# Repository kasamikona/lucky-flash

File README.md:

# Lucky Guitar Flashcart
A custom flashcart for the Lucky Group electronic guitar toy (らっき組 ギター) RK-001, made by People Co., Ltd.  

## What's it for?
The guitar toy, which I will call the Lucky Guitar from here onwards, has multiple play modes.
One of these modes uses ROM cartridges containing songs which you can play along with.
The songs are stored as MIDI files containing chord information.  

There were 14 main cartridges made, focusing on certain genres or artists,
and an additional "demo" cartridge containing a compilation of songs from the others.
The Lucky Guitar came with 2 or 3 random cartridges in the box, though additional ones could be purchased.
As it was a relatively obscure device, the cartridges are quite rare and it is very hard to collect them all.  

To allow the Lucky Guitar to be enjoyed to its fullest, I have developed a flash cart based heavily on the original cartridge design.
It supports playing ROM dumps of existing cartridges, as well as custom ROMs made from your own suitable MIDI files.
The latest version supports up to 8 different ROMs on one cartridge, with DIP switches to select them.  

Due to their small size, the flash carts contain no active logic and must be programmed externally.
Currently this is done through a custom adapter stackup for the TL866 (aka "MiniPro") Universal Programmer.
The stackup consists of a SN001-1 aka TSOP48 V3 base board from XinGong Tech, and the custom cartridge interface from here.
This adapter stack also allows dumping ROMs from the original cartridges after some modifications.  

## Contents
The main files you will want for making and using the flash cart are:
- **CartFlashMulti**: the latest multi-bank flash cart with DIP switches, intended for use with the custom shell. Gerber files coming soon.
- **LuckyCartInterface-TL866**: flash programmer interface for the TL866 and SN001-1. Gerber files coming soon.
- **CartShell.scad**: custom cart shell for the multi-bank flash cart, designed for SLA 3D printing. Render the main and cover parts separately. STL files coming soon.
- **CartParts.kicad_sym / CartParts.pretty**: custom KiCad parts shared between all PCBs.

The repo contains these additional files:
- **CartReplica**: a copy of the original cart PCB for research and analysis.
- **CartFlashSingle**: a flash cart based on the original carts, with minimal changes to support externally programming a flash chip. This can fit in an original shell.
- **DIP48-SN001**: a helper board that theoretically allows the cart interface to be used on other programming devices with 48-pin sockets.

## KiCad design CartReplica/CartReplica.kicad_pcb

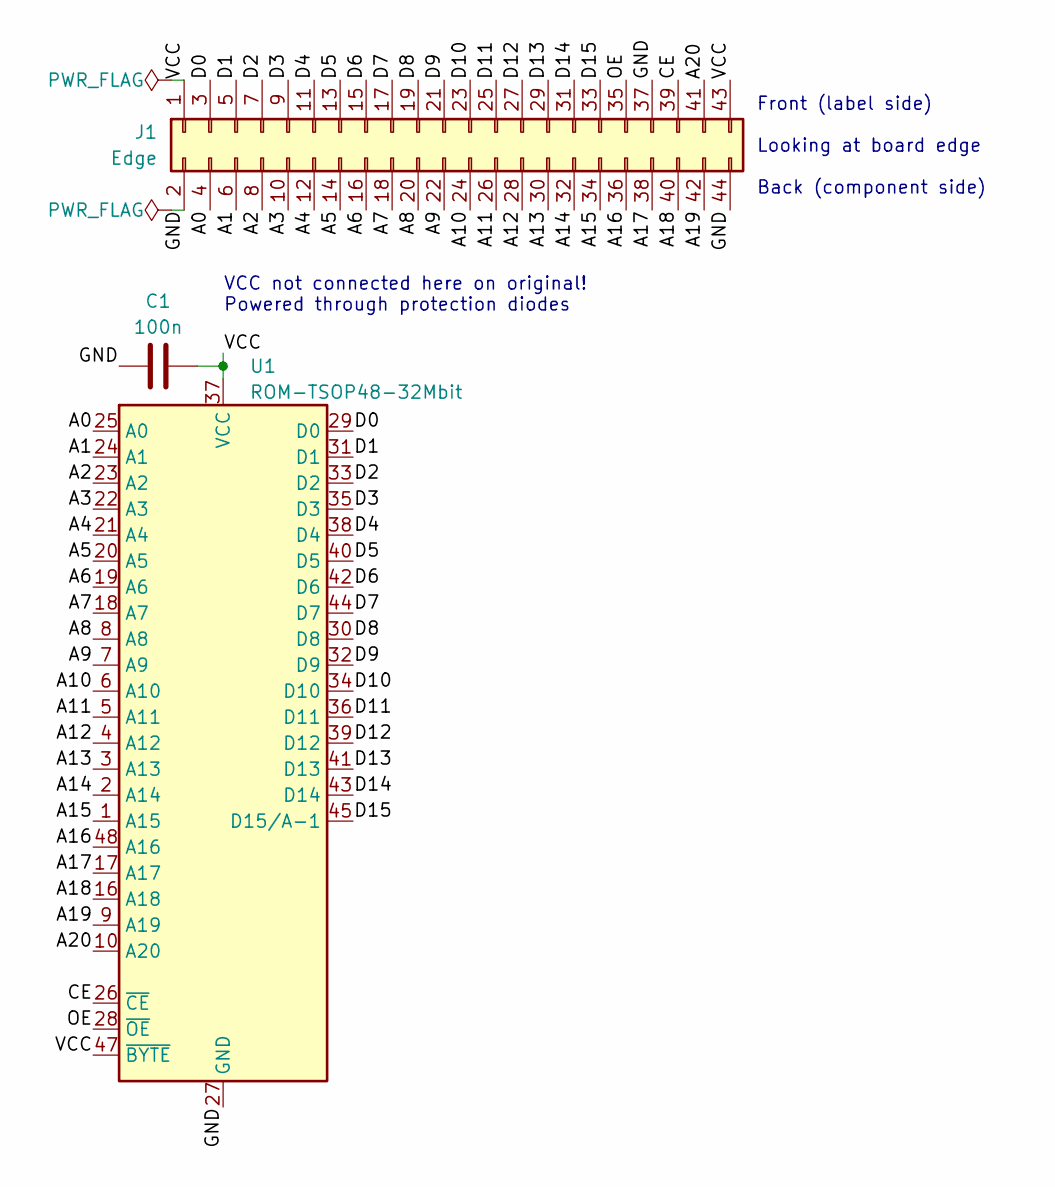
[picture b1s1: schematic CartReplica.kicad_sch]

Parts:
C1: 100n; C_0603_1608Metric_Pad1.08x0.95mm_HandSolder
J1: Edge; LuckyCartEdge
U1: ROM-TSOP48-32Mbit; TSOP-I-48_18.4x12mm_P0.5mm

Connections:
/A0: J1.4, U1.25 (A0)
/A1: J1.6, U1.24 (A1)
/A2: J1.8, U1.23 (A2)
/A3: J1.10, U1.22 (A3)
/A4: J1.12, U1.21 (A4)
/A5: J1.14, U1.20 (A5)
/A6: J1.16, U1.19 (A6)
/A7: J1.18, U1.18 (A7)
/A8: J1.20, U1.8 (A8)
/A9: J1.22, U1.7 (A9)
/A10: J1.24, U1.6 (A10)
/A11: J1.26, U1.5 (A11)
/A12: J1.28, U1.4 (A12)
/A13: J1.30, U1.3 (A13)
/A14: J1.32, U1.2 (A14)
/A15: J1.34, U1.1 (A15)
/A16: J1.36, U1.48 (A16)
/A17: J1.38, U1.17 (A17)
/A18: J1.40, U1.16 (A18)
/A19: J1.42, U1.9 (A19)
/A20: J1.41, U1.10 (A20)
/CE: J1.39, U1.26 (~CE)
/D0: J1.3, U1.29 (D0)
/D1: J1.5, U1.31 (D1)
/D2: J1.7, U1.33 (D2)
/D3: J1.9, U1.35 (D3)
/D4: J1.11, U1.38 (D4)
/D5: J1.13, U1.40 (D5)
/D6: J1.15, U1.42 (D6)
/D7: J1.17, U1.44 (D7)
/D8: J1.19, U1.30 (D8)
/D9: J1.21, U1.32 (D9)
/D10: J1.23, U1.34 (D10)
/D11: J1.25, U1.36 (D11)
/D12: J1.27, U1.39 (D12)
/D13: J1.29, U1.41 (D13)
/D14: J1.31, U1.43 (D14)
/D15: J1.33, U1.45 (D15/A-1)
/OE: J1.35, U1.28 (~OE)
/VCC: C1.1, J1.1, J1.43, U1.37 (VCC), U1.47 (~BYTE)
GND: C1.2, J1.2, J1.37, J1.44, U1.27 (GND), U1.46 (GND)

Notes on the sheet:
VCC not connected here on original! Powered through protection diodes
Front (label side) Looking at board edge Back (component side)

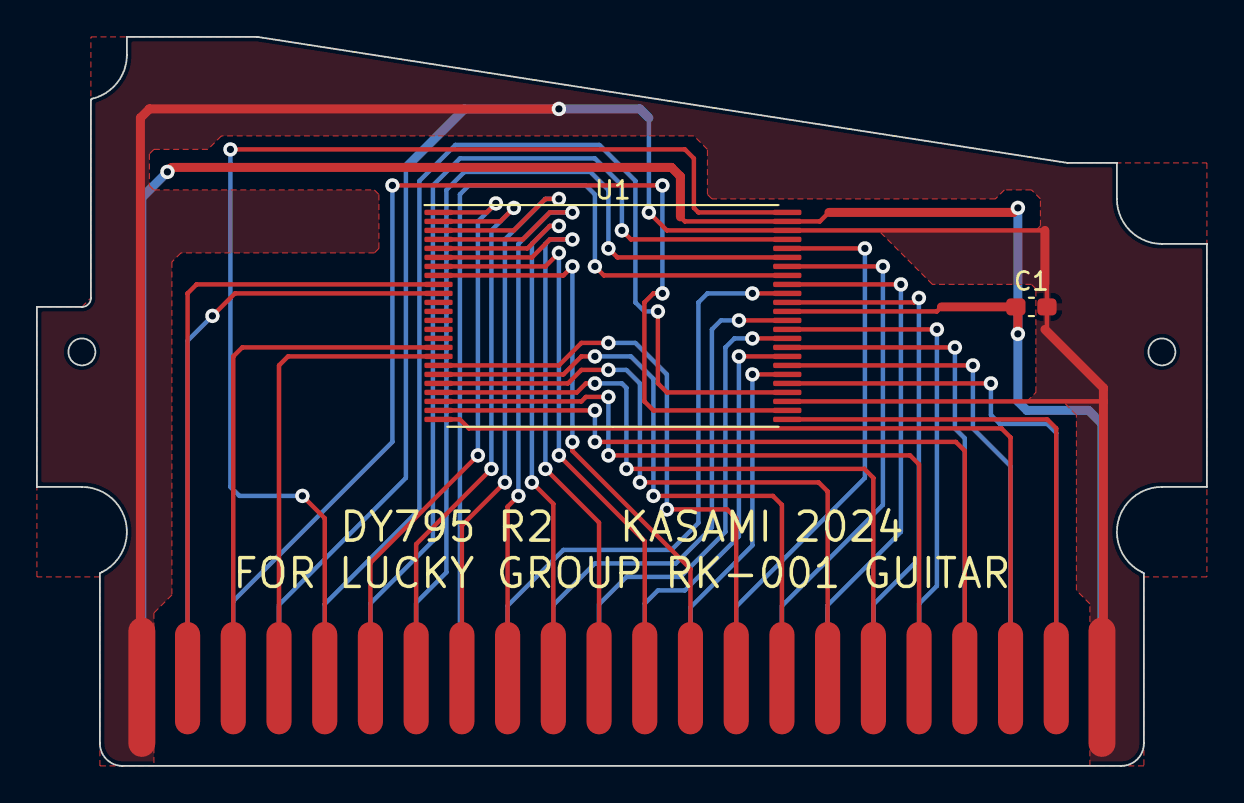
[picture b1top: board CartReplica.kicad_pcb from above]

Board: 2 copper layers, 65.0 x 40.5 mm, 3 parts (1 on the bottom side), 41 nets.

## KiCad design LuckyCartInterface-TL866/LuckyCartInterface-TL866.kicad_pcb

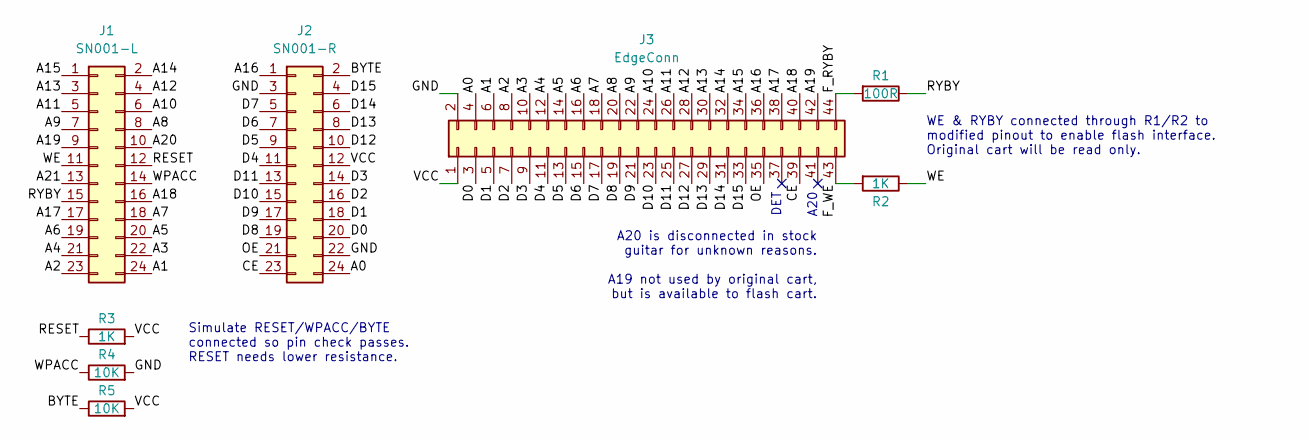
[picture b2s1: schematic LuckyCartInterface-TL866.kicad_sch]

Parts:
J1: SN001-L; PinSocket_2x12_P2.54mm_Vertical
J2: SN001-R; PinSocket_2x12_P2.54mm_Vertical
J3: EdgeConn; TE_Standard-Edge-II_44P
R1: 100R; R_0603_1608Metric_Pad0.98x0.95mm_HandSolder
R2, R3: 1K; R_0603_1608Metric_Pad0.98x0.95mm_HandSolder
R4, R5: 10K; R_0603_1608Metric_Pad0.98x0.95mm_HandSolder

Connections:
/A0: J2.24, J3.4
/A1: J1.24, J3.6
/A2: J1.23, J3.8
/A3: J1.22, J3.10
/A4: J1.21, J3.12
/A5: J1.20, J3.14
/A6: J1.19, J3.16
/A7: J1.18, J3.18
/A8: J1.8, J3.20
/A9: J1.7, J3.22
/A10: J1.6, J3.24
/A11: J1.5, J3.26
/A12: J1.4, J3.28
/A13: J1.3, J3.30
/A14: J1.2, J3.32
/A15: J1.1, J3.34
/A16: J2.1, J3.36
/A17: J1.17, J3.38
/A18: J1.16, J3.40
/A19: J1.9, J3.42
/A20: J1.10
/A21: J1.13
/BYTE: J2.2, R5.1
/CE: J2.23, J3.39
/D0: J2.20, J3.3
/D1: J2.18, J3.5
/D2: J2.16, J3.7
/D3: J2.14, J3.9
/D4: J2.11, J3.11
/D5: J2.9, J3.13
/D6: J2.7, J3.15
/D7: J2.5, J3.17
/D8: J2.19, J3.19
/D9: J2.17, J3.21
/D10: J2.15, J3.23
/D11: J2.13, J3.25
/D12: J2.10, J3.27
/D13: J2.8, J3.29
/D14: J2.6, J3.31
/D15: J2.4, J3.33
/F_RYBY: J3.44, R1.2
/F_WE: J3.43, R2.2
/GND: J2.3, J2.22, J3.2, R4.2
/OE: J2.21, J3.35
/RESET: J1.12, R3.1
/RYBY: J1.15, R1.1
/VCC: J2.12, J3.1, R3.2, R5.2
/WE: J1.11, R2.1
/WPACC: J1.14, R4.1

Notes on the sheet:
WE & RYBY connected through R1/R2 to modified pinout to enable flash interface. Original cart will be read only.
DET
A20 is disconnected in stock guitar for unknown reasons. A19 not used by original cart, but is available to flash cart.
Simulate RESET/WPACC/BYTE connected so pin check passes. RESET needs lower resistance.
A20

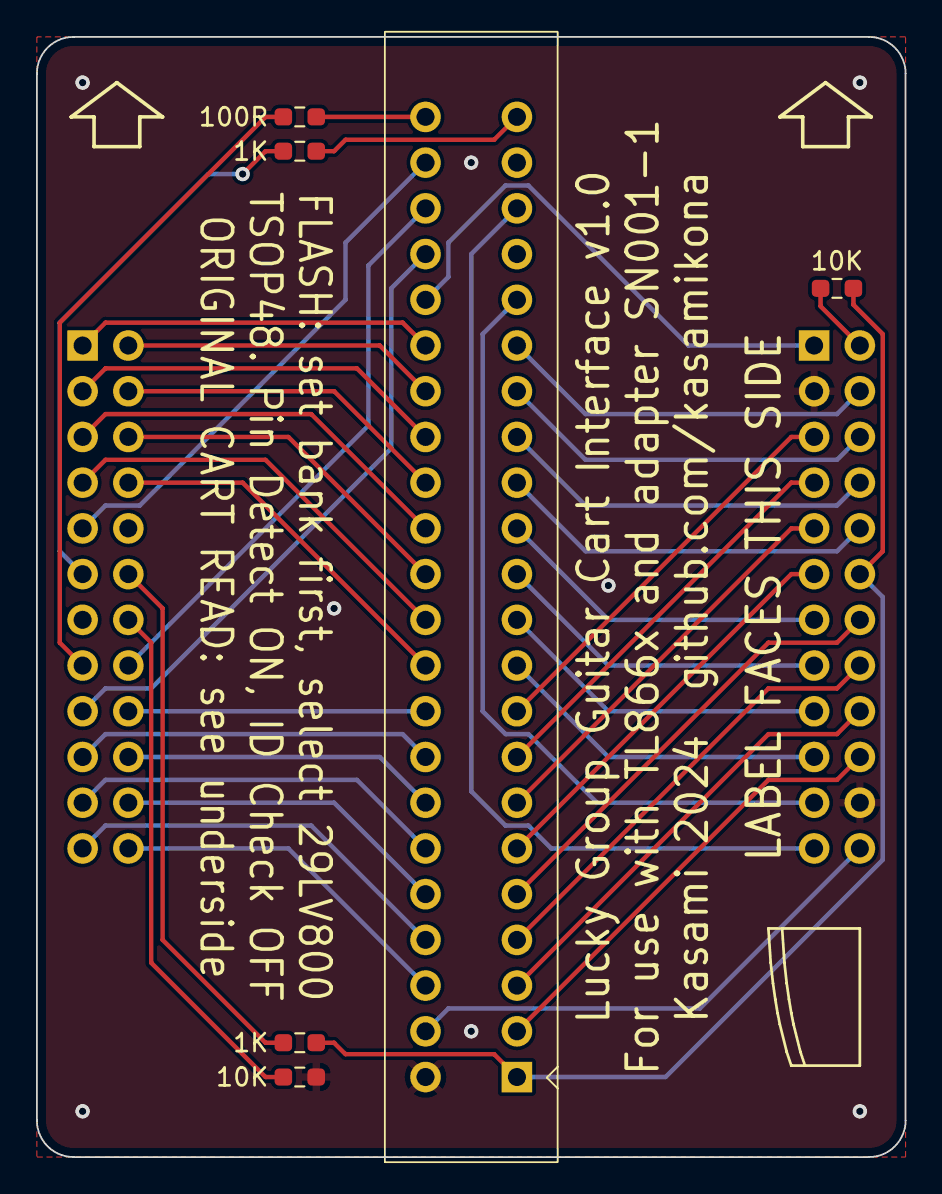
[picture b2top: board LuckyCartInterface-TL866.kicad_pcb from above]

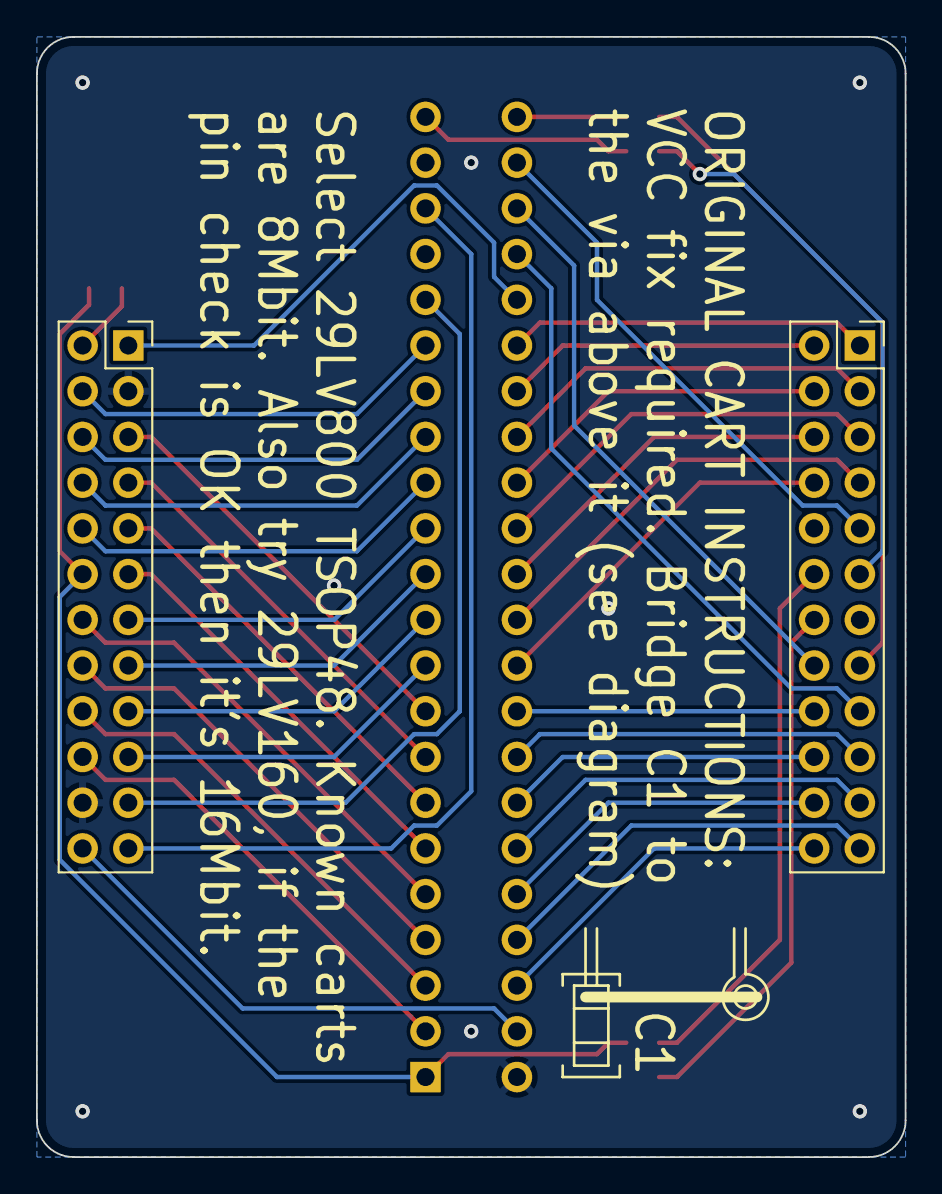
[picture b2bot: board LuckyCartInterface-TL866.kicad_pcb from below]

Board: 2 copper layers, 48.3 x 62.2 mm, 8 parts (2 on the bottom side), 47 nets.

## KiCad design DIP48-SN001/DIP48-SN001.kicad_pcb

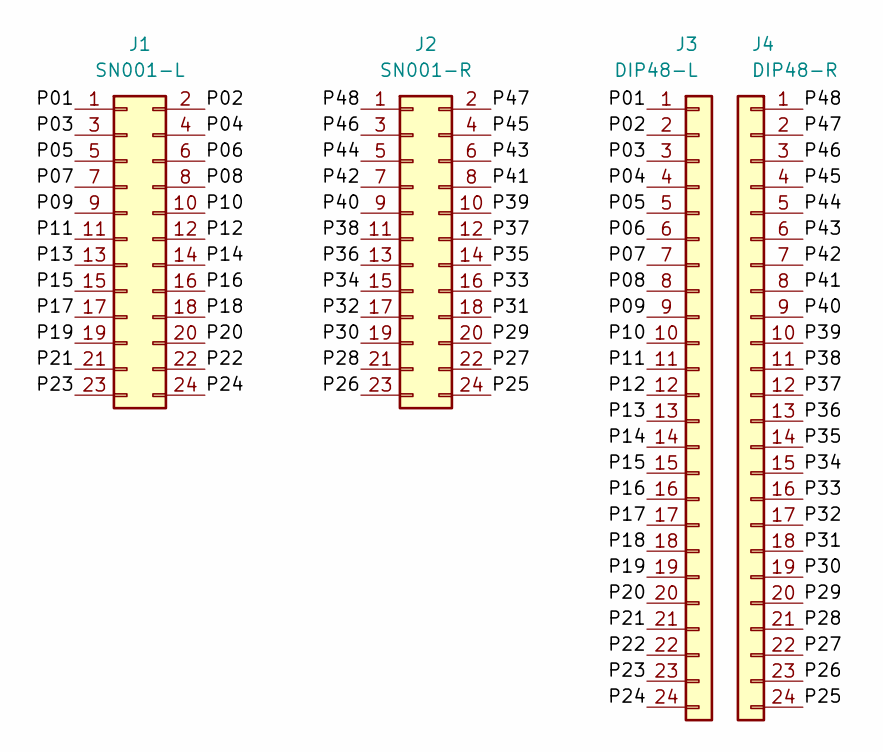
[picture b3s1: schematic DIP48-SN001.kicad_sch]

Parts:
J1: SN001-L; PinHeader_2x12_P2.54mm_Vertical
J2: SN001-R; PinHeader_2x12_P2.54mm_Vertical
J3: DIP48-L; PinHeader_1x24_P2.54mm_Vertical
J4: DIP48-R; PinHeader_1x24_P2.54mm_Vertical

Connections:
/P01: J1.1, J3.1
/P02: J1.2, J3.2
/P03: J1.3, J3.3
/P04: J1.4, J3.4
/P05: J1.5, J3.5
/P06: J1.6, J3.6
/P07: J1.7, J3.7
/P08: J1.8, J3.8
/P09: J1.9, J3.9
/P10: J1.10, J3.10
/P11: J1.11, J3.11
/P12: J1.12, J3.12
/P13: J1.13, J3.13
/P14: J1.14, J3.14
/P15: J1.15, J3.15
/P16: J1.16, J3.16
/P17: J1.17, J3.17
/P18: J1.18, J3.18
/P19: J1.19, J3.19
/P20: J1.20, J3.20
/P21: J1.21, J3.21
/P22: J1.22, J3.22
/P23: J1.23, J3.23
/P24: J1.24, J3.24
/P25: J2.24, J4.24
/P26: J2.23, J4.23
/P27: J2.22, J4.22
/P28: J2.21, J4.21
/P29: J2.20, J4.20
/P30: J2.19, J4.19
/P31: J2.18, J4.18
/P32: J2.17, J4.17
/P33: J2.16, J4.16
/P34: J2.15, J4.15
/P35: J2.14, J4.14
/P36: J2.13, J4.13
/P37: J2.12, J4.12
/P38: J2.11, J4.11
/P39: J2.10, J4.10
/P40: J2.9, J4.9
/P41: J2.8, J4.8
/P42: J2.7, J4.7
/P43: J2.6, J4.6
/P44: J2.5, J4.5
/P45: J2.4, J4.4
/P46: J2.3, J4.3
/P47: J2.2, J4.2
/P48: J2.1, J4.1

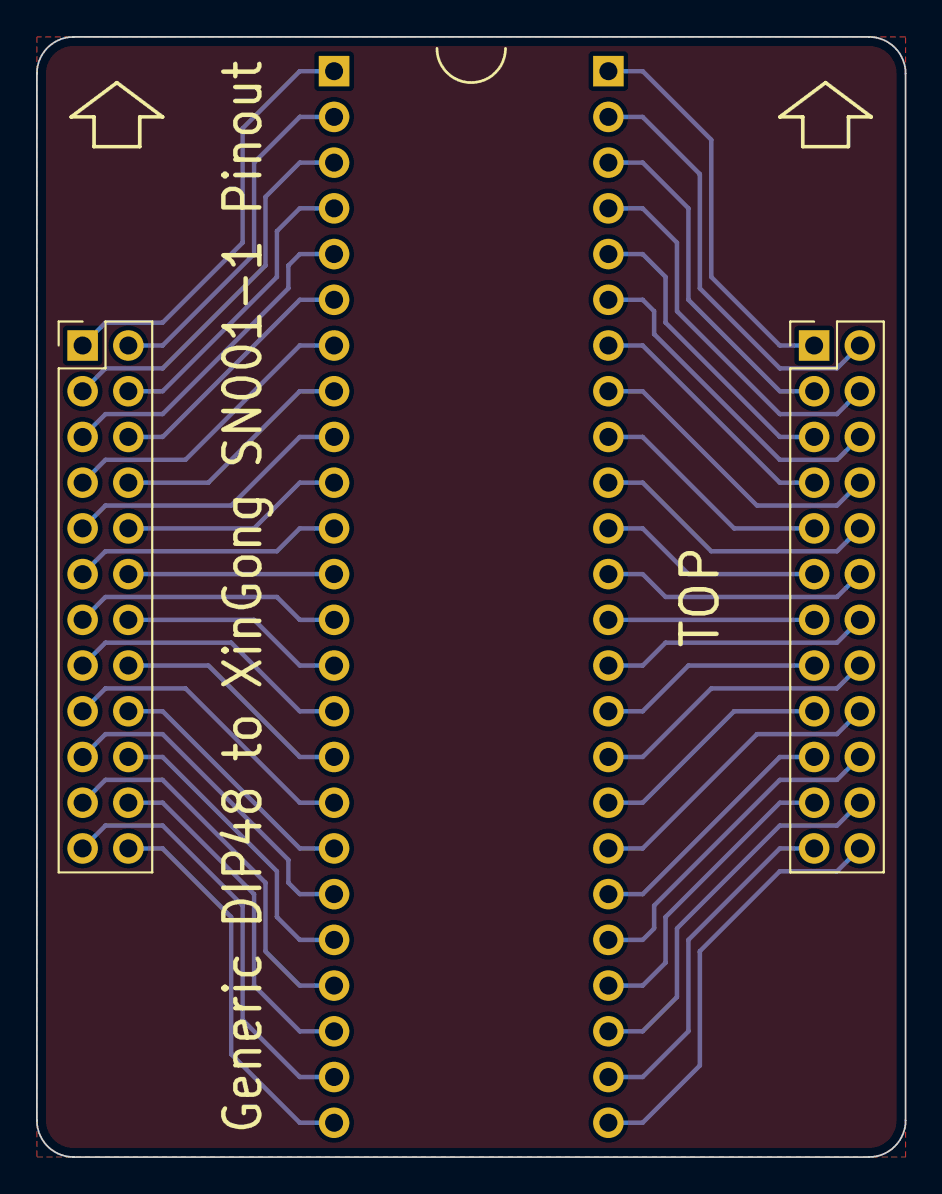
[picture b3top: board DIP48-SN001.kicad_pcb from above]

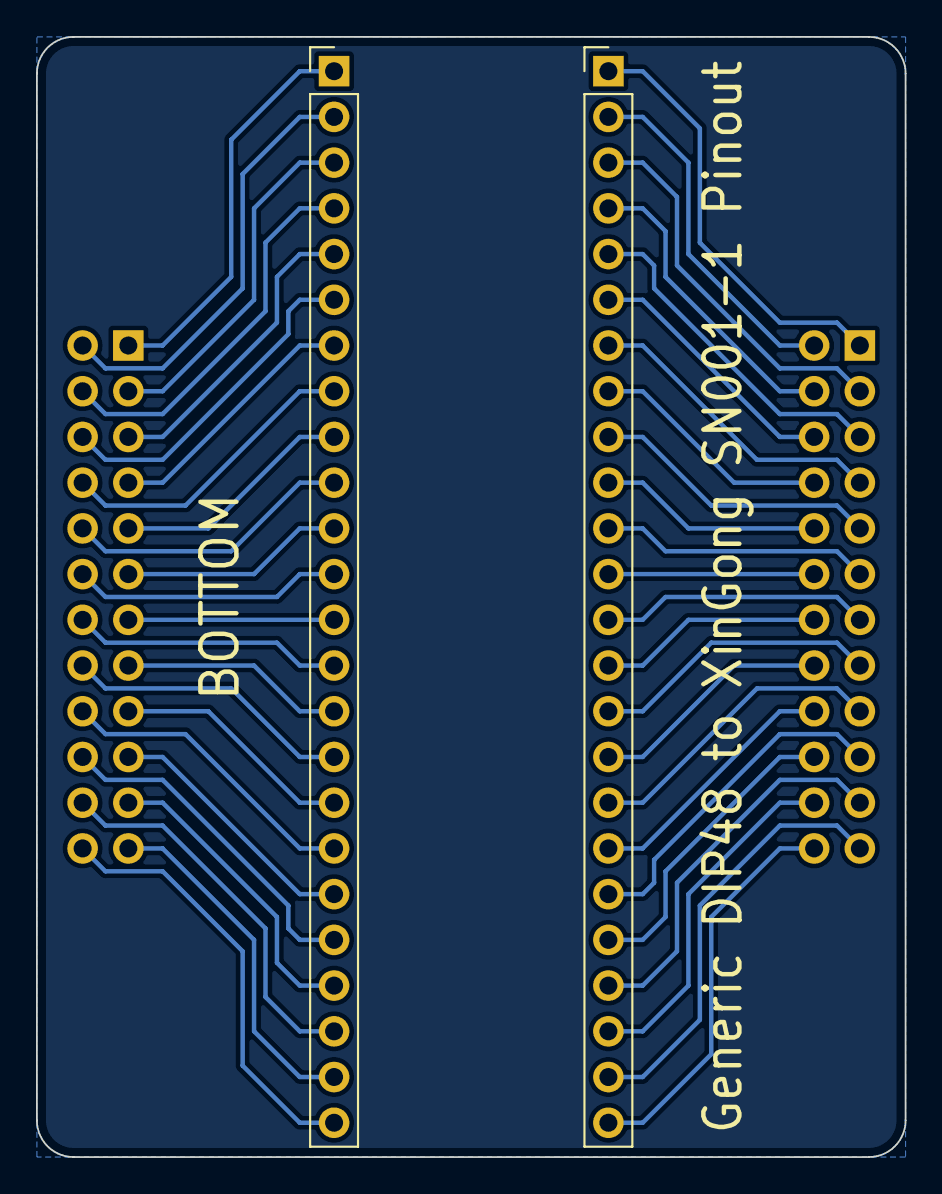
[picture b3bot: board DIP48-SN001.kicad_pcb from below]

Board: 2 copper layers, 48.3 x 62.2 mm, 4 parts (2 on the bottom side), 48 nets.

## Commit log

2024-12-19 Publish v1.0 files to git
2024-12-20 Add rom format info
